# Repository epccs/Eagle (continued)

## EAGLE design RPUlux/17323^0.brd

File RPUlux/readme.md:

# RPUlux

This circuit board has six 330mA LED channels each done with AL8805W5-7, it uses the ATmega328p's six PWM pins to control the switch mode current sources that can be enabled and disabled at 500Hz. A few pins also go to other connectors and allow some digital input-output or analog input options. The IO is also level shifted to work with the two onboard current sources.

[Software]

[Software]: https://github.com/epccs/RPUlux/

[Bom]

[Bom]: https://github.com/epccs/RPUlux/

[OSHPark]s

[OSHPark]: https://oshpark.com/shared_projects/fMLOXrKi

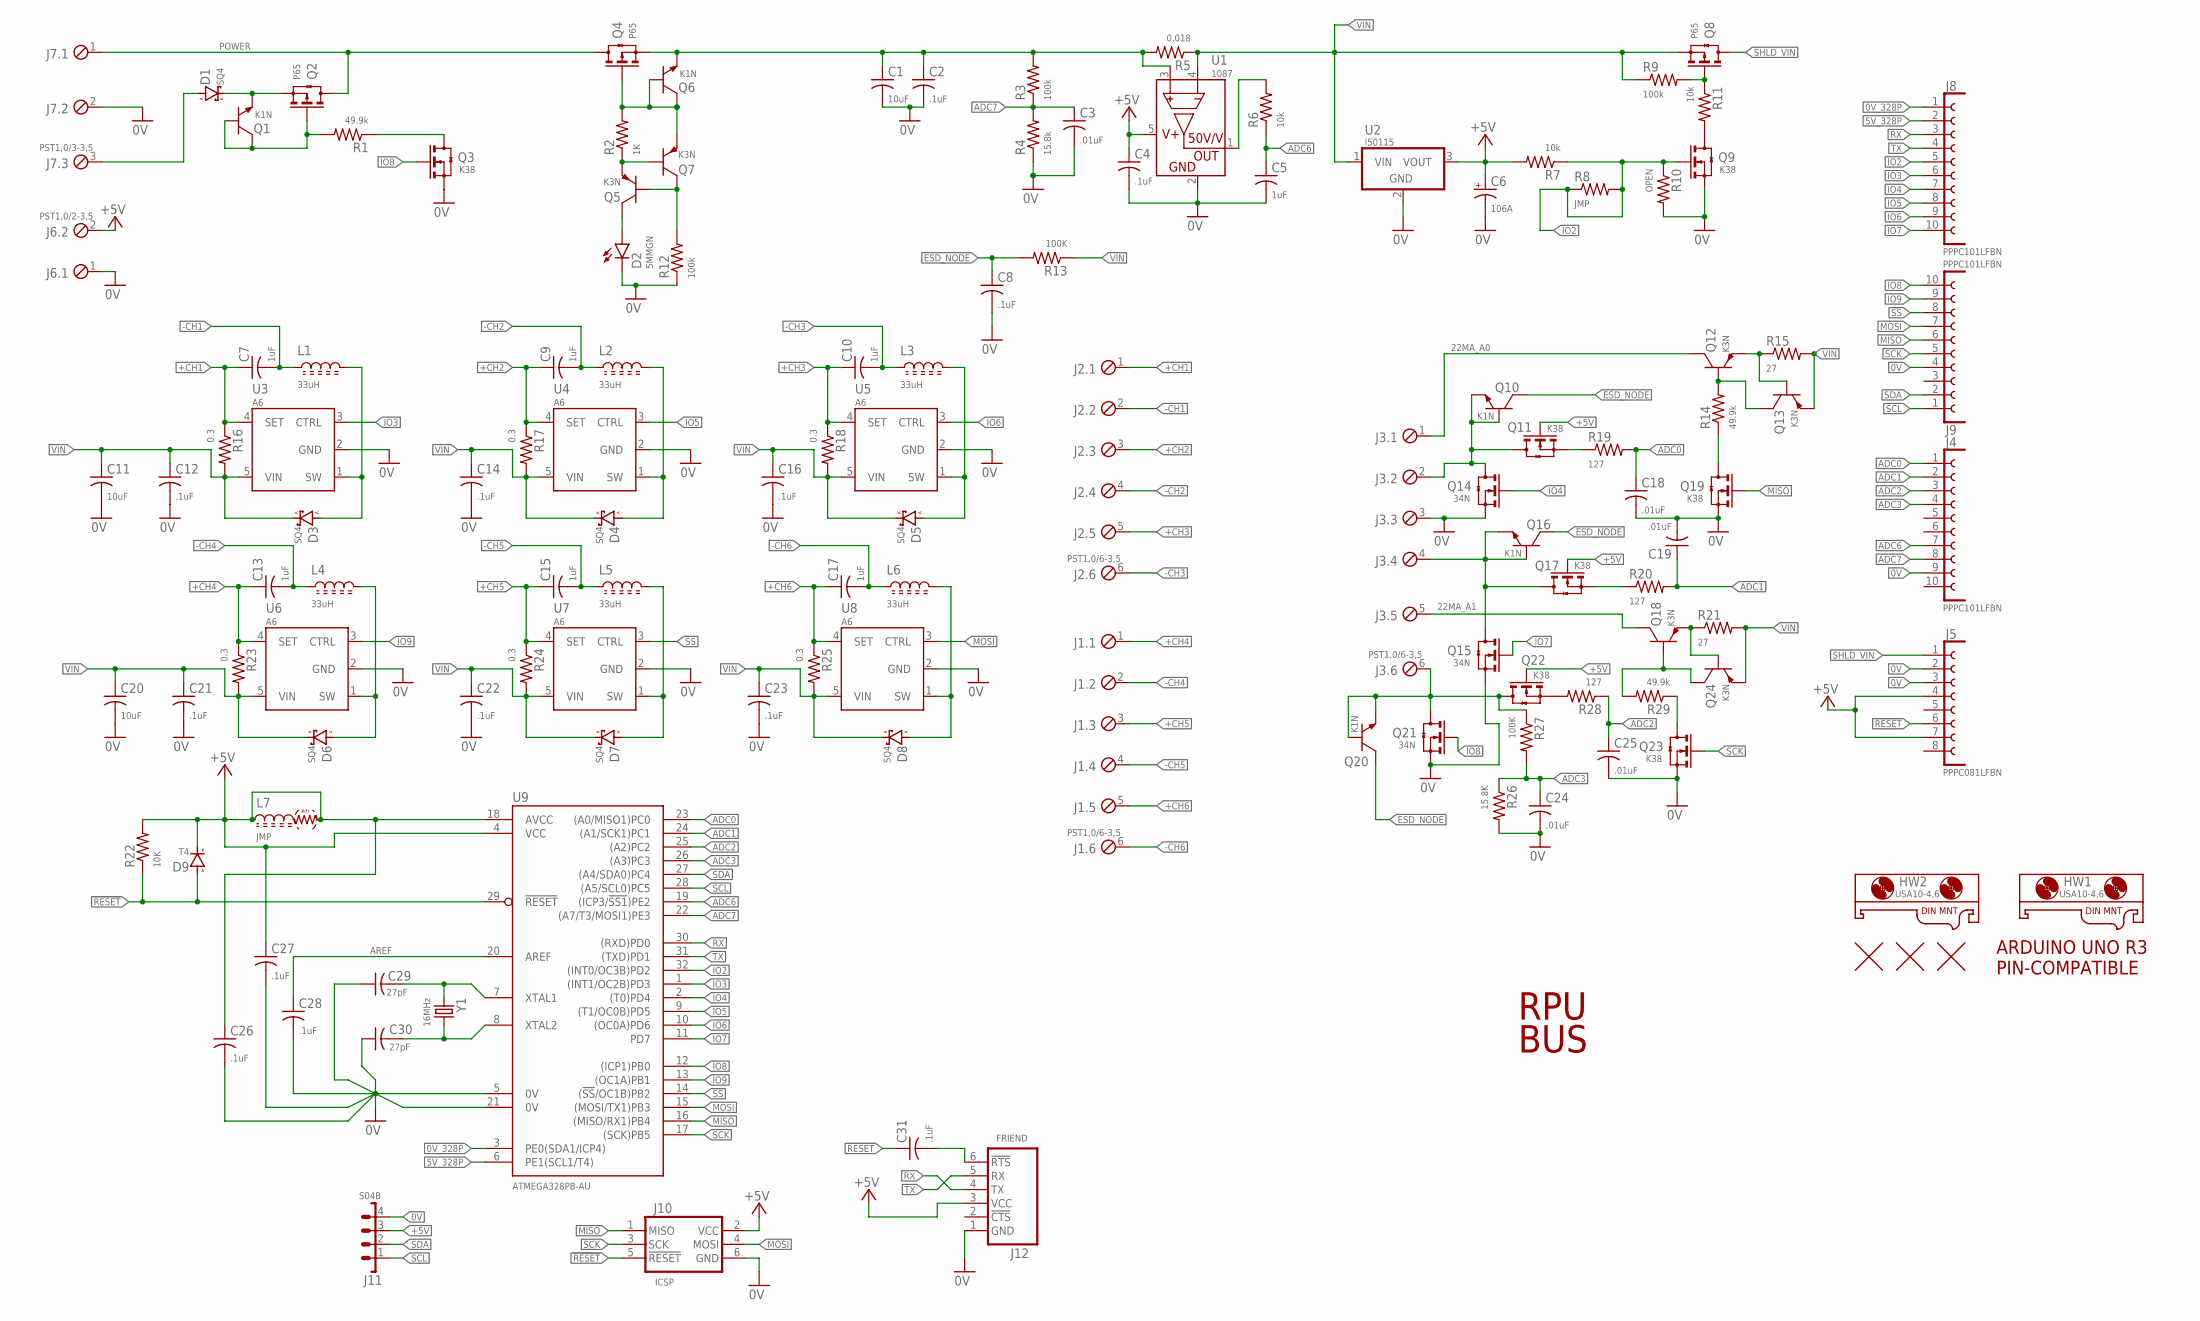
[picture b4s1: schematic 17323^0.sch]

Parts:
C1, C11, C20: 10uF; C1206(3216)
C2: .1uF; C0805(2012)
C3, C18, C19, C24, C25: .01uF; C0603(1608)
C4, C8, C12, C14, C16, C21, C22, C23, C26, C27, C28, C31: .1uF; C0603(1608)
C5, C7, C9, C10, C13, C15, C17: 1uF; C0805(2012)
C6: 106A; 3216
C29, C30: 27pF; C0603(1608)
D1, D3, D4, D5, D6, D7, D8: SQ4; SMA
D2: 5MMGN; LED5MM
D9: T4; SOD123
HW1, HW2: USA10-4,6; USA10
J1, J2, J3: PST1,0/6-3,5; MCV6
J4, J8, J9: PPPC101LFBN; F1X10
J5: PPPC081LFBN; F1X8
J6: PST1,0/2-3,5; MCV2
J7: PST1,0/3-3,5; MCV3
J10: ICSP; ISP
J11: S04B; B04B
J12: FRIEND
L1, L2, L3, L4, L5, L6: 33uH; L2424
L7: JMP; C0805(2012)
Q1, Q6, Q10, Q16, Q20: K1N; SOT23
Q2, Q4, Q8: P65; SOT23
Q3, Q9, Q11, Q17, Q19, Q22, Q23: K38; SOT23
Q5, Q7, Q12, Q13, Q18, Q24: K3N; SOT23
Q14, Q15, Q21: 34N; SOT23
R1, R14, R29: 49.9k; C0805(2012)
R2: 1K; C0805(2012)
R3, R9, R12: 100k; C0805(2012)
R4: 15.8k; C0805(2012)
R5: 0.018; C1210(3225)
R6, R7, R11: 10k; C0805(2012)
R8: JMP; C0805(2012)
R10: OPEN; C0805(2012)
R13, R27: 100K; C0805(2012)
R15, R21: 27; C0805(2012)
R16, R17, R18, R23, R24, R25: 0.3; C1210(3225)
R19, R20, R28: 127; C0805(2012)
R22: 10K; C0805(2012)
R26: 15.8K; C0805(2012)
U1: 1087; SOT23-5
U2: I50115; OKI-78SR-H
U3, U4, U5, U6, U7, U8: A6; SOT23-5
U9: ATMEGA328PB-AU; TQFP32-08
U$1: ARDUINO-UNO; ARDUINO_UNO
U$2, U$3, U$4: FIDUCIAL1.27; FIDUCIAL-1.27
Y1: 16MHz; CSM-3X

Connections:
0V: C1.2, C2.2, C3.2, C4.2, C5.2, C6.-, C8.2, C11.2, C12.2, C14.2, C16.2, C18.2, C19.2, C20.2, C21.2, C22.2, C23.2, C24.2, C25.2, C26.2, C27.2, C28.2, C29.1, C30.1, D2.K, J3.3, J4.9, J5.2, J5.3, J6.1, J7.2, J9.4, J10.6 (GND), J11.4, J12.1 (GND), Q3.2(S) (S), Q9.2(S) (S), Q14.2(S) (S), Q15.2(S) (S), Q19.2(S) (S), Q21.2(S) (S), Q23.2(S) (S), R4.1, R10.2, R12.1, R26.2, U1.2 (GND), U2.2 (GND), U3.2 (GND), U4.2 (GND), U5.2 (GND), U6.2 (GND), U7.2 (GND), U8.2 (GND), U9.5 (0V), U9.21 (0V)
0V_328P: J8.1, U9.3 (PE0(SDA1/ICP4))
5V_328P: J8.2, U9.6 (PE1(SCL1/T4))
22MA_A0: J3.1, Q12.C
22MA_A1: J3.5, Q18.C
!RESET!: C31.1, D9.A, J5.6, J10.5 (!RESET), R22.1, U9.29 (!RESET)
!SS: J9.8, U7.3 (CTRL), U9.14 ((!SS!/OC1B)PB2)
+5V: C4.1, C6.+, C26.1, C27.1, D9.C (K), J5.4, J5.7, J6.2, J10.2 (VCC), J11.3, J12.3 (VCC), L7.1, L7.2, Q11.1(G) (G), Q17.1(G) (G), Q22.1(G) (G), R7.2, R22.2, U1.5 (VCC), U2.3 (VOUT), U9.4 (VCC), U9.18 (AVCC)
+CH1: C7.1, J2.1, R16.1, U3.4 (SET)
+CH2: C9.1, J2.3, R17.1, U4.4 (SET)
+CH3: C10.1, J2.5, R18.1, U5.4 (SET)
+CH4: C13.1, J1.1, R23.1, U6.4 (SET)
+CH5: C15.1, J1.3, R24.1, U7.4 (SET)
+CH6: C17.1, J1.5, R25.1, U8.4 (SET)
-CH1: C7.2, J2.2, L1.1
-CH2: C9.2, J2.4, L2.1
-CH3: C10.2, J2.6, L3.1
-CH4: C13.2, J1.2, L4.1
-CH5: C15.2, J1.4, L5.1
-CH6: C17.2, J1.6, L6.1
ADC0: C18.1, J4.1, R19.2, U9.23 ((A0/MISO1)PC0)
ADC1: C19.1, J4.2, R20.2, U9.24 ((A1/SCK1)PC1)
ADC2: C25.1, J4.3, R28.1, U9.25 ((A2)PC2)
ADC3: C24.1, J4.4, R26.1, R27.2, U9.26 ((A3)PC3)
ADC6: C5.1, J4.7, R6.1, U9.19 ((ICP3/!SS1!)PE2)
ADC7: C3.1, J4.8, R3.1, R4.2, U9.22 ((A7/T3/MOSI1)PE3)
AREF: C28.1, U9.20 (AREF)
ESD_NODE: C8.1, Q10.C, Q16.C, Q20.C, R13.2
IO2: J8.5, Q9.1(G) (G), R7.1, R8.1, R8.2, R10.1, U9.32 ((INT0/OC3B)PD2)
IO3: J8.6, U3.3 (CTRL), U9.1 ((INT1/OC2B)PD3)
IO4: J8.7, Q14.1(G) (G), U9.2 ((T0)PD4)
IO5: J8.8, U4.3 (CTRL), U9.9 ((T1/OC0B)PD5)
IO6: J8.9, U5.3 (CTRL), U9.10 ((OC0A)PD6)
IO7: J8.10, Q15.1(G) (G), U9.11 (PD7)
IO8: J9.10, Q3.1(G) (G), Q21.1(G) (G), U9.12 ((ICP1)PB0)
IO9: J9.9, U6.3 (CTRL), U9.13 ((OC1A)PB1)
MISO: J9.6, J10.1 (MISO), Q19.1(G) (G), U9.16 ((MISO/RX1)PB4)
MOSI: J9.7, J10.4 (MOSI), U8.3 (CTRL), U9.15 ((MOSI/TX1)PB3)
unnamed: Q22.2(S) (S), R28.2
unnamed: Q8.1(G) (G), R9.2, R11.1
unnamed: D3.A, L1.2, U3.1 (SW)
unnamed: Q9.3(D) (D), R11.2
unnamed: Q5.B, Q7.C, R12.2
unnamed: Q4.1(G) (G), Q6.B, Q6.C, Q7.E, R2.2
unnamed: D2.A, Q5.C
unnamed: R6.2, U1.1 (OUT)
unnamed: J3.6, Q20.B, Q20.E, Q21.3(D) (D), Q22.3(D) (D), R27.1
unnamed: Q5.E, Q7.B, R2.1
unnamed: D6.A, L4.2, U6.1 (SW)
unnamed: J3.4, Q15.3(D) (D), Q16.B, Q16.E, Q17.3(D) (D)
unnamed: Q17.2(S) (S), R20.1
unnamed: Q11.2(S) (S), R19.1
unnamed: J3.2, Q10.B, Q10.E, Q11.3(D) (D), Q14.3(D) (D)
unnamed: D4.A, L2.2, U4.1 (SW)
unnamed: D7.A, L5.2, U7.1 (SW)
unnamed: D5.A, L3.2, U5.1 (SW)
unnamed: Q23.3(D) (D), R29.1
unnamed: Q12.E, Q13.B, R15.1
unnamed: Q19.3(D) (D), R14.1
unnamed: D8.A, L6.2, U8.1 (SW)
unnamed: Q12.B, Q13.C, R14.2
unnamed: D1.A, J7.3
unnamed: C31.2, J12.6 (!RTS)
unnamed: Q18.E, Q24.B, R21.1
unnamed: Q18.B, Q24.C, R29.2
unnamed: D1.K, Q1.E, Q2.2(S) (S)
unnamed: Q1.B, Q1.C, Q2.1(G) (G), R1.2
unnamed: Q3.3(D) (D), R1.1
unnamed: C29.2, U9.7 (XTAL1), Y1.1
unnamed: C30.2, U9.8 (XTAL2), Y1.2
POWER: J7.1, Q2.3(D) (D), Q4.3(D) (D)
RX: J8.3, J12.4 (TX), U9.30 ((RXD)PD0)
SCK: J9.5, J10.3 (SCK), Q23.1(G) (G), U9.17 ((SCK)PB5)
SCL: J9.1, J11.1, U9.28 ((A5/SCL0)PC5)
SDA: J9.2, J11.2, U9.27 ((A4/SDA0)PC4)
SHLD_VIN: J5.1, Q8.3(D) (D)
TX: J8.4, J12.5 (RX), U9.31 ((TXD)PD1)
VIN: C11.1, C12.1, C14.1, C16.1, C20.1, C21.1, C22.1, C23.1, D3.K, D4.K, D5.K, D6.K, D7.K, D8.K, Q8.2(S) (S), Q13.E, Q24.E, R5.1, R9.1, R13.1, R15.2, R16.2, R17.2, R18.2, R21.2, R23.2, R24.2, R25.2, U1.4 (S-), U2.1 (VIN), U3.5 (VIN), U4.5 (VIN), U5.5 (VIN), U6.5 (VIN), U7.5 (VIN), U8.5 (VIN)
VIN_S: C1.1, C2.1, Q4.2(S) (S), Q6.E, R3.2, R5.2, U1.3 (S+)

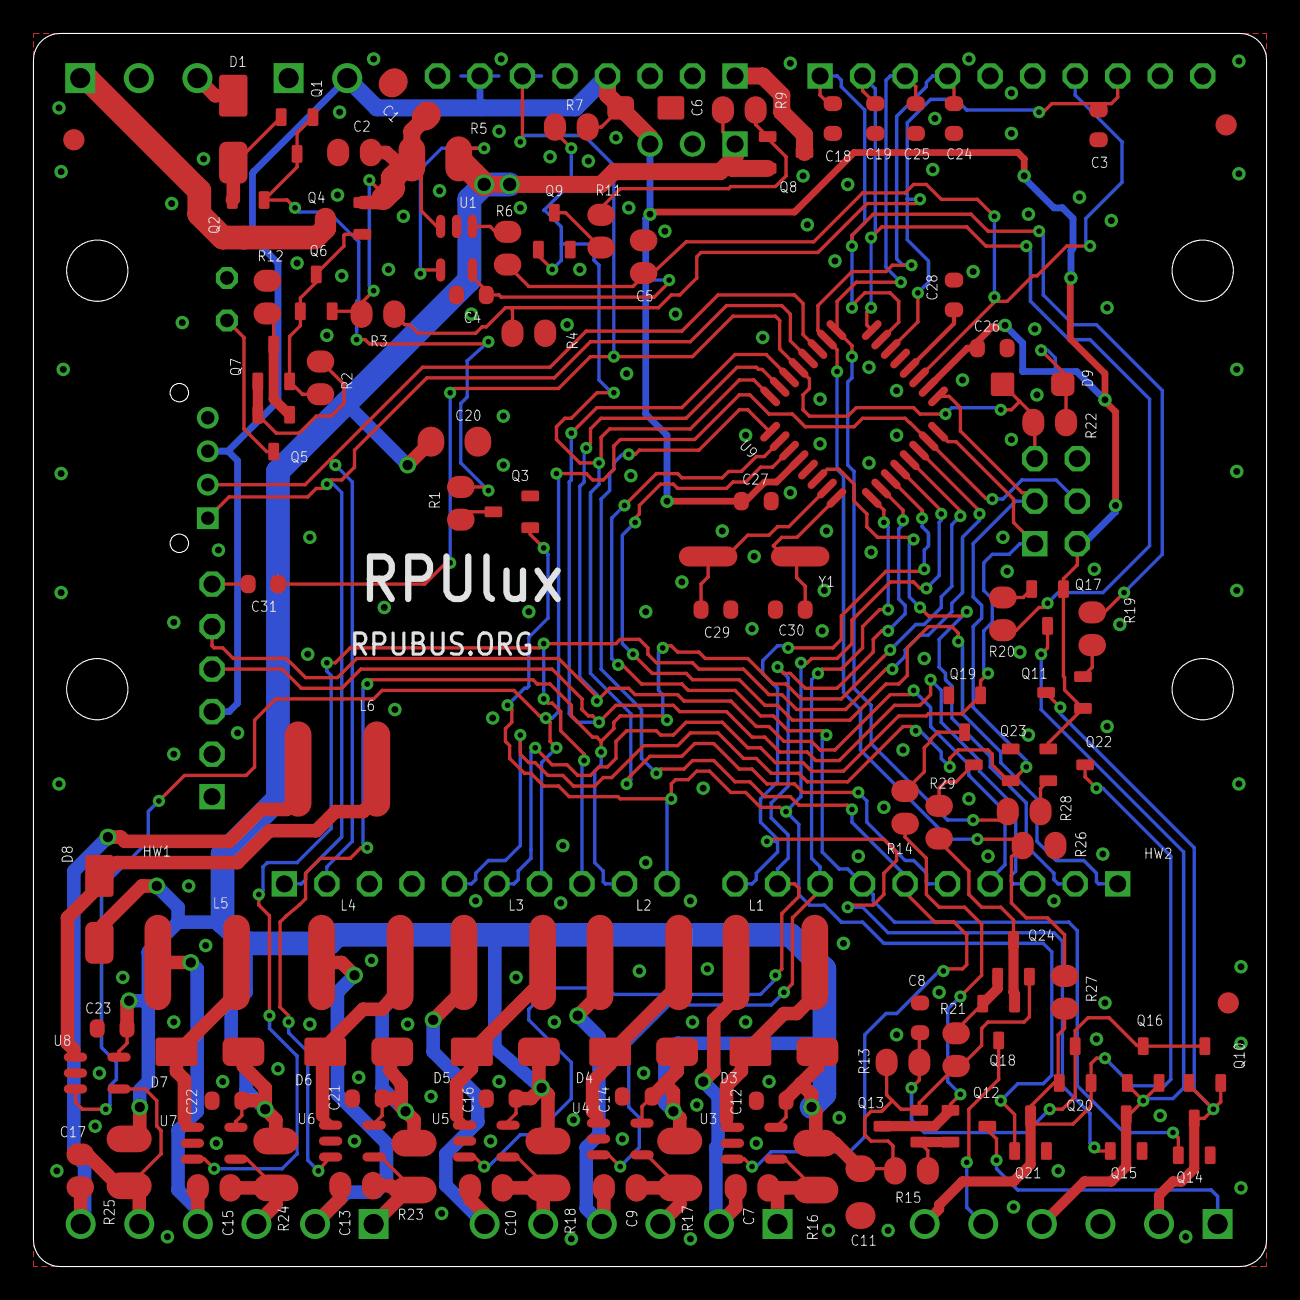
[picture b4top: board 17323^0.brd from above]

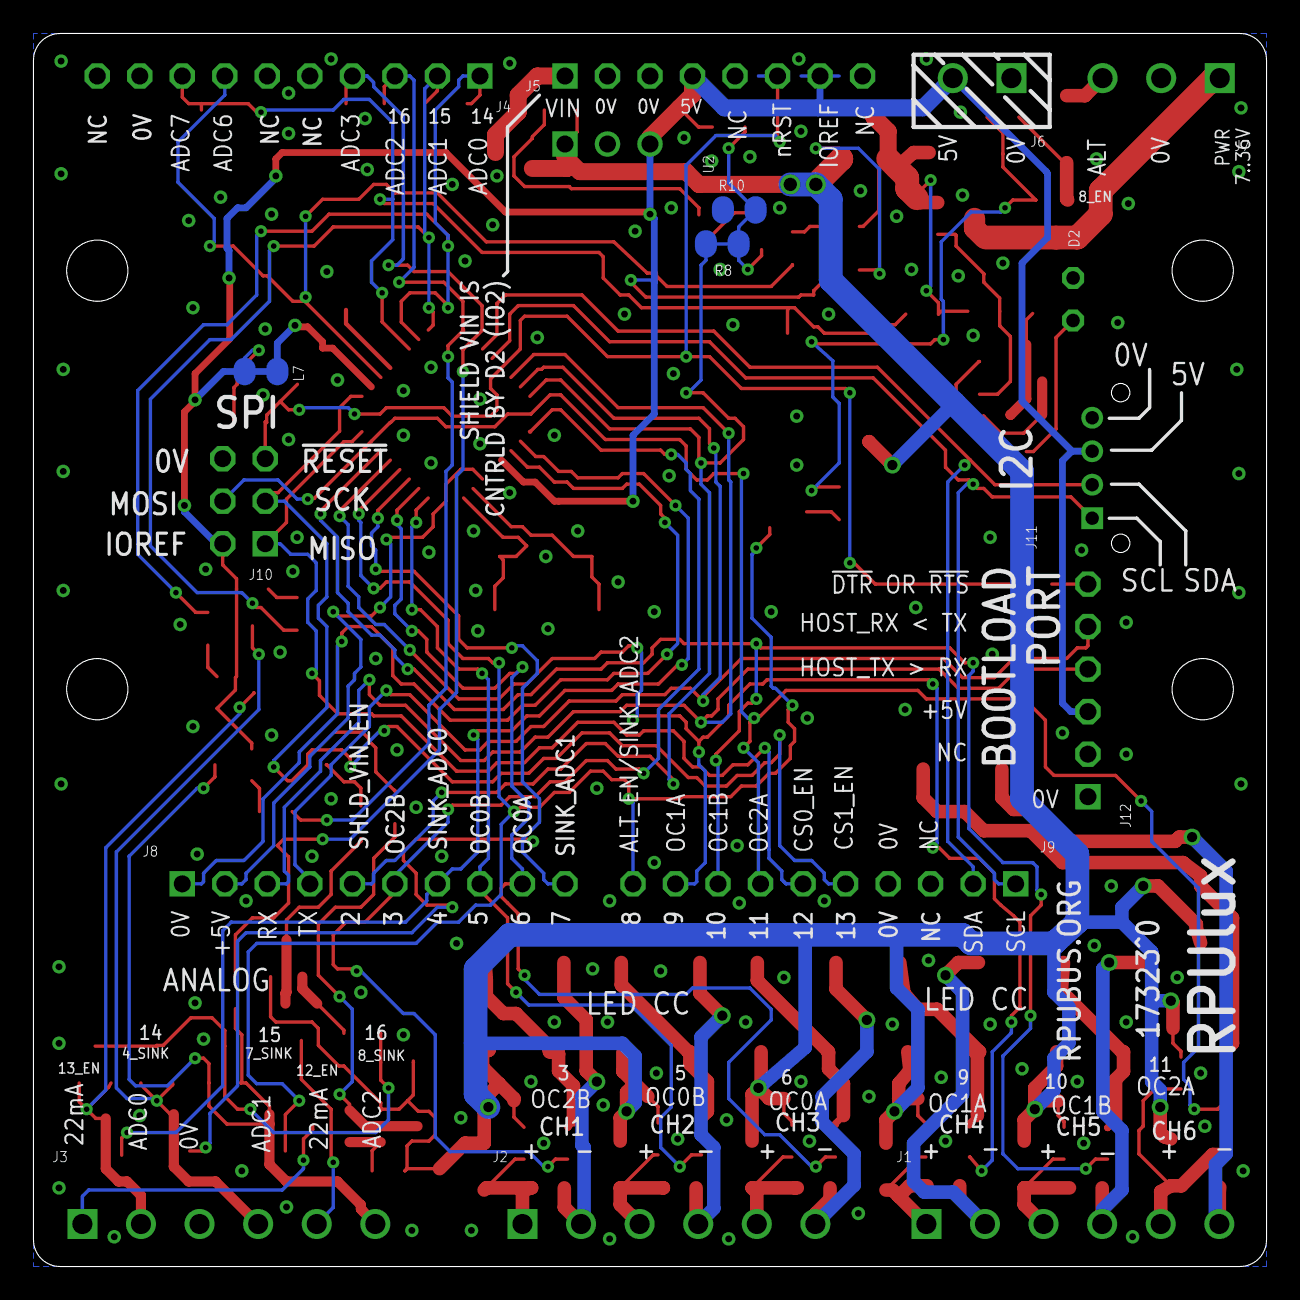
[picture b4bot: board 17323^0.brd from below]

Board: 2 copper layers, 73.7 x 73.7 mm, 128 parts (18 on the bottom side), 79 nets.

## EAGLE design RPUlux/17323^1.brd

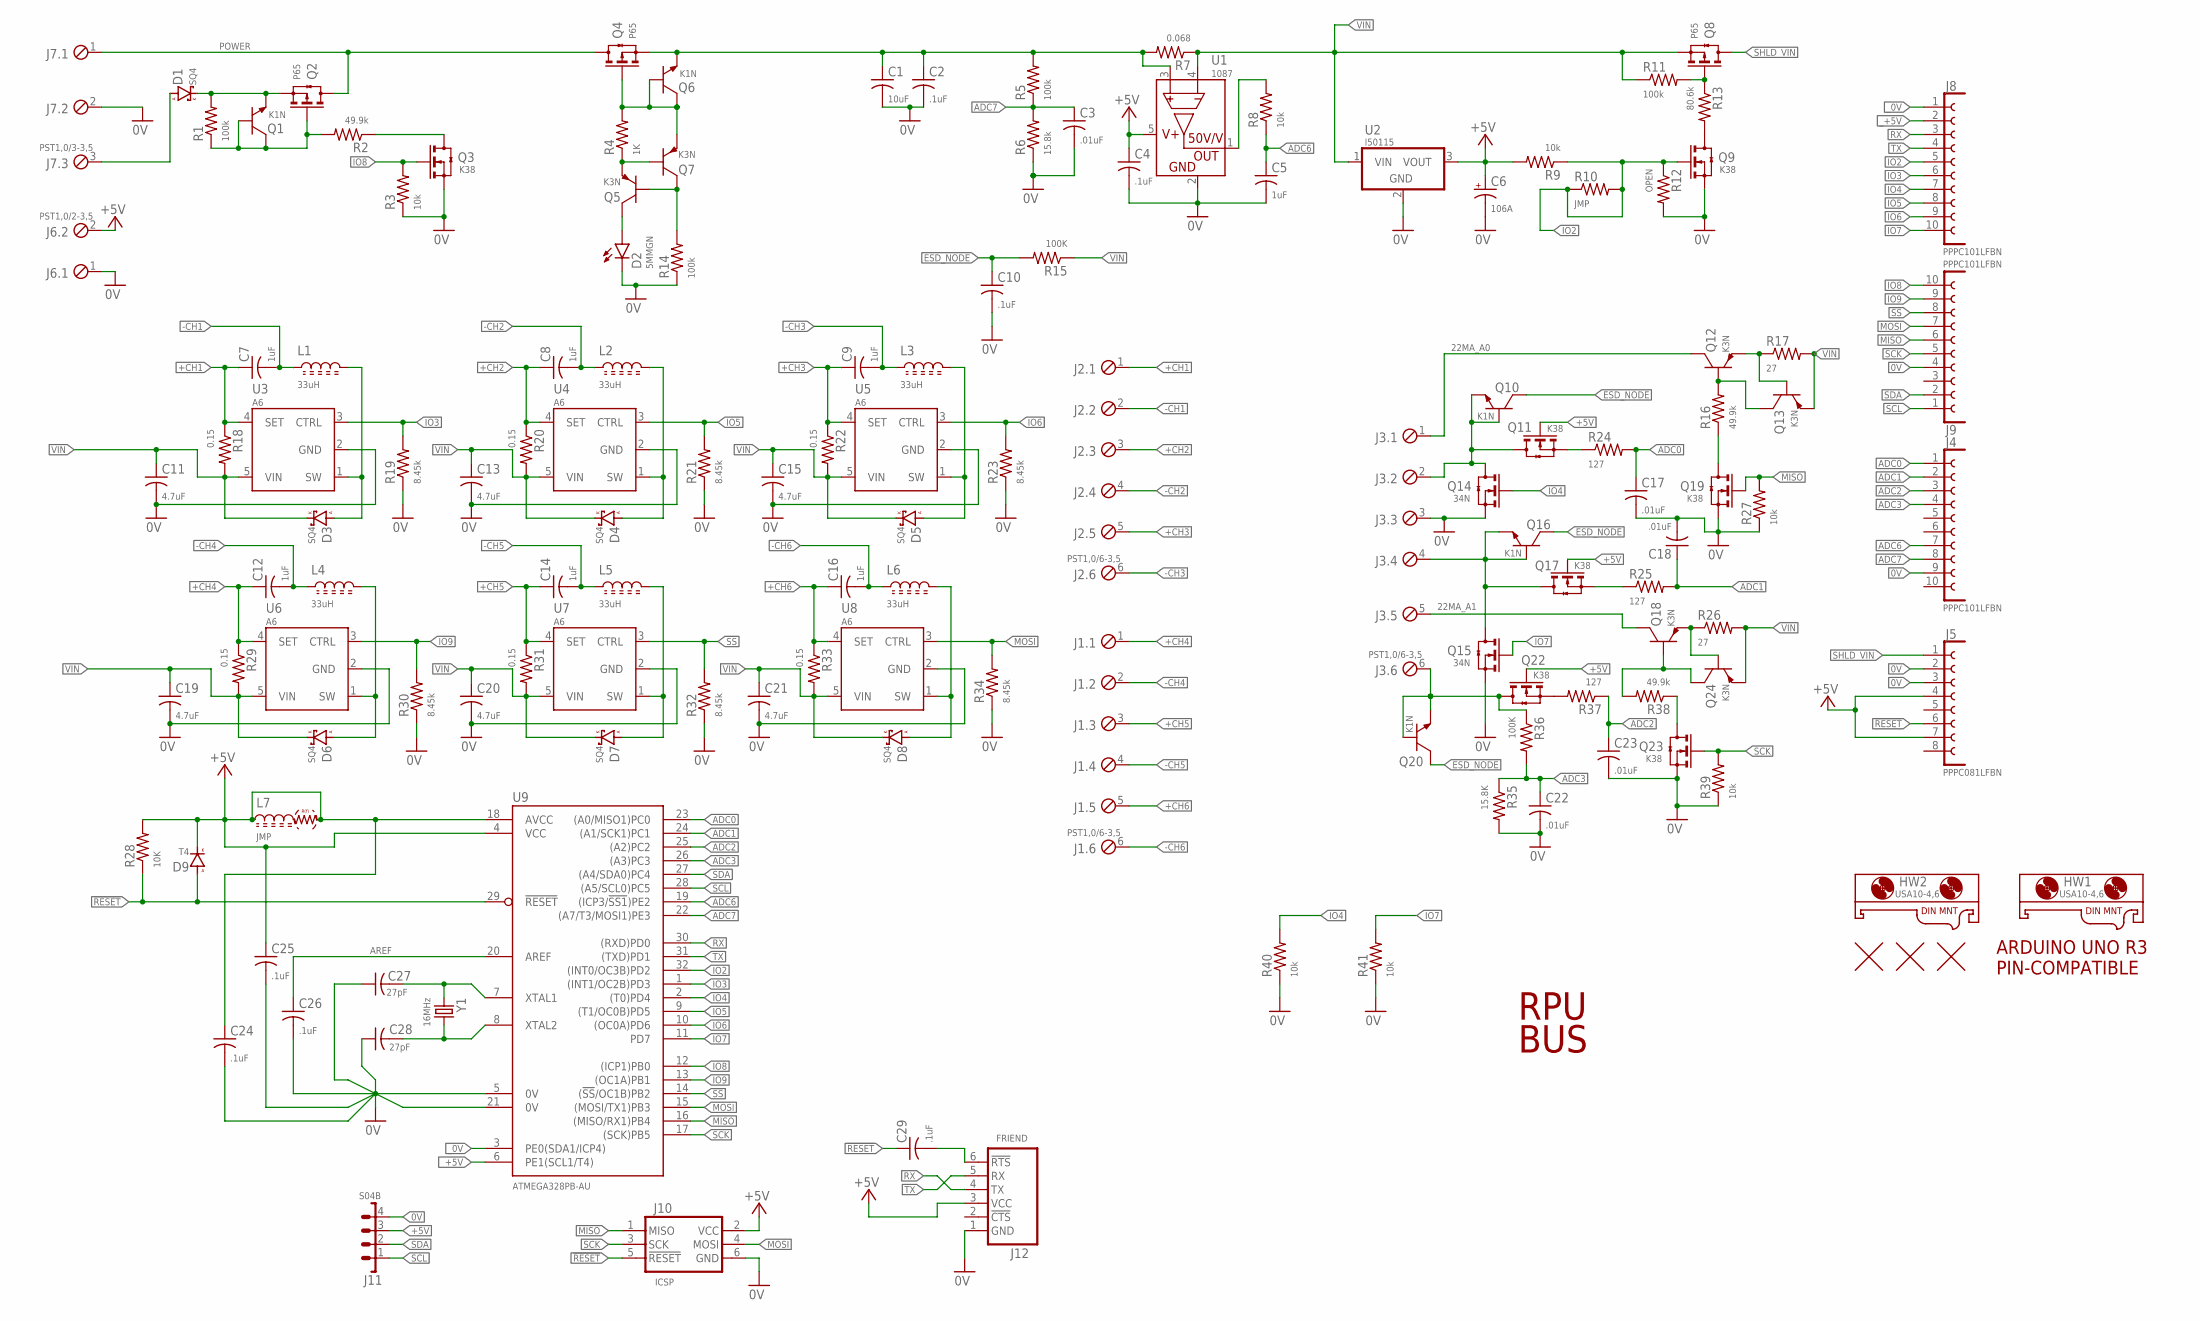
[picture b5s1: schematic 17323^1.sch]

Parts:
C1: 10uF; C1206(3216)
C2: .1uF; C0805(2012)
C3, C17, C18, C22, C23: .01uF; C0603(1608)
C4, C10, C24, C25, C26, C29: .1uF; C0603(1608)
C5, C7, C8, C9, C12, C14, C16: 1uF; C0805(2012)
C6: 106A; 3216
C11, C13, C15, C19, C20, C21: 4.7uF; C1206(3216)
C27, C28: 27pF; C0603(1608)
D1, D3, D4, D5, D6, D7, D8: SQ4; SMA
D2: 5MMGN; LED5MM
D9: T4; SOD123
HW1, HW2: USA10-4,6; USA10
J1, J2, J3: PST1,0/6-3,5; MCV6
J4, J8, J9: PPPC101LFBN; F1X10
J5: PPPC081LFBN; F1X8
J6: PST1,0/2-3,5; MCV2
J7: PST1,0/3-3,5; MCV3
J10: ICSP; ISP
J11: S04B; B04B
J12: FRIEND
L1, L2, L3, L4, L5, L6: 33uH; L2424
L7: JMP; C0805(2012)
Q1, Q6, Q10, Q16, Q20: K1N; SOT23
Q2, Q4, Q8: P65; SOT23
Q3, Q9, Q11, Q17, Q19, Q22, Q23: K38; SOT23
Q5, Q7, Q12, Q13, Q18, Q24: K3N; SOT23
Q14, Q15: 34N; SOT23
R1, R5, R11, R14: 100k; C0805(2012)
R2, R16, R38: 49.9k; C0805(2012)
R3, R8, R9, R27, R39, R40, R41: 10k; C0805(2012)
R4: 1K; C0805(2012)
R6: 15.8k; C0805(2012)
R7: 0.068; C1210(3225)
R10: JMP; C0805(2012)
R12: OPEN; C0805(2012)
R13: 80.6k; C0805(2012)
R15, R36: 100K; C0805(2012)
R17, R26: 27; C0805(2012)
R18, R20, R22, R29, R31, R33: 0.15; C1210(3225)
R19, R21, R23, R30, R32, R34: 8.45k; C0805(2012)
R24, R25, R37: 127; C0805(2012)
R28: 10K; C0805(2012)
R35: 15.8K; C0805(2012)
U1: 1087; SOT23-5
U2: I50115; OKI-78SR-H
U3, U4, U5, U6, U7, U8: A6; SOT23-5
U9: ATMEGA328PB-AU; TQFP32-08
U$1: ARDUINO-UNO; ARDUINO_UNO
U$2, U$3, U$4: FIDUCIAL1.27; FIDUCIAL-1.27
Y1: 16MHz; CSM-3X

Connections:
0V: C1.2, C2.2, C3.2, C4.2, C5.2, C6.-, C10.2, C11.2, C13.2, C15.2, C17.2, C18.2, C19.2, C20.2, C21.2, C22.2, C23.2, C24.2, C25.2, C26.2, C27.1, C28.1, D2.K, J3.3, J4.9, J5.2, J5.3, J6.1, J7.2, J9.4, J10.6 (GND), J11.4, J12.1 (GND), Q3.2(S) (S), Q9.2(S) (S), Q14.2(S) (S), Q15.2(S) (S), Q19.2(S) (S), Q23.2(S) (S), R3.1, R6.1, R12.2, R14.1, R19.1, R21.1, R23.1, R27.1, R30.1, R32.1, R34.1, R35.2, R39.1, R40.1, R41.1, U1.2 (GND), U2.2 (GND), U3.2 (GND), U4.2 (GND), U5.2 (GND), U6.2 (GND), U7.2 (GND), U8.2 (GND), U9.5 (0V), U9.21 (0V)
22MA_A0: J3.1, Q12.C
22MA_A1: J3.5, Q18.C
!RESET!: C29.1, D9.A, J5.6, J10.5 (!RESET), R28.1, U9.29 (!RESET)
!SS: J9.8, R32.2, U7.3 (CTRL), U9.14 ((!SS!/OC1B)PB2)
+5V: C4.1, C6.+, C24.1, C25.1, D9.C (K), J5.4, J5.7, J6.2, J10.2 (VCC), J11.3, J12.3 (VCC), L7.1, L7.2, Q11.1(G) (G), Q17.1(G) (G), Q22.1(G) (G), R9.2, R28.2, U1.5 (VCC), U2.3 (VOUT), U9.4 (VCC), U9.18 (AVCC)
+CH1: C7.1, J2.1, R18.1, U3.4 (SET)
+CH2: C8.1, J2.3, R20.1, U4.4 (SET)
+CH3: C9.1, J2.5, R22.1, U5.4 (SET)
+CH4: C12.1, J1.1, R29.1, U6.4 (SET)
+CH5: C14.1, J1.3, R31.1, U7.4 (SET)
+CH6: C16.1, J1.5, R33.1, U8.4 (SET)
-CH1: C7.2, J2.2, L1.1
-CH2: C8.2, J2.4, L2.1
-CH3: C9.2, J2.6, L3.1
-CH4: C12.2, J1.2, L4.1
-CH5: C14.2, J1.4, L5.1
-CH6: C16.2, J1.6, L6.1
ADC0: C17.1, J4.1, R24.2, U9.23 ((A0/MISO1)PC0)
ADC1: C18.1, J4.2, R25.2, U9.24 ((A1/SCK1)PC1)
ADC2: C23.1, J4.3, R37.1, U9.25 ((A2)PC2)
ADC3: C22.1, J4.4, R35.1, R36.2, U9.26 ((A3)PC3)
ADC6: C5.1, J4.7, R8.1, U9.19 ((ICP3/!SS1!)PE2)
ADC7: C3.1, J4.8, R5.1, R6.2, U9.22 ((A7/T3/MOSI1)PE3)
AREF: C26.1, U9.20 (AREF)
ESD_NODE: C10.1, Q10.C, Q16.C, Q20.C, R15.2
IO2: J8.5, Q9.1(G) (G), R9.1, R10.1, R10.2, R12.1, U9.32 ((INT0/OC3B)PD2)
IO3: J8.6, R19.2, U3.3 (CTRL), U9.1 ((INT1/OC2B)PD3)
IO4: J8.7, Q14.1(G) (G), R40.2, U9.2 ((T0)PD4)
IO5: J8.8, R21.2, U4.3 (CTRL), U9.9 ((T1/OC0B)PD5)
IO6: J8.9, R23.2, U5.3 (CTRL), U9.10 ((OC0A)PD6)
IO7: J8.10, Q15.1(G) (G), R41.2, U9.11 (PD7)
IO8: J9.10, Q3.1(G) (G), R3.2, U9.12 ((ICP1)PB0)
IO9: J9.9, R30.2, U6.3 (CTRL), U9.13 ((OC1A)PB1)
MISO: J9.6, J10.1 (MISO), Q19.1(G) (G), R27.2, U9.16 ((MISO/RX1)PB4)
MOSI: J9.7, J10.4 (MOSI), R34.2, U8.3 (CTRL), U9.15 ((MOSI/TX1)PB3)
unnamed: Q22.2(S) (S), R37.2
unnamed: Q8.1(G) (G), R11.2, R13.1
unnamed: D3.A, L1.2, U3.1 (SW)
unnamed: Q9.3(D) (D), R13.2
unnamed: Q5.B, Q7.C, R14.2
unnamed: Q4.1(G) (G), Q6.B, Q6.C, Q7.E, R4.2
unnamed: D2.A, Q5.C
unnamed: R8.2, U1.1 (OUT)
unnamed: J3.6, Q20.B, Q20.E, Q22.3(D) (D), R36.1
unnamed: Q5.E, Q7.B, R4.1
unnamed: D6.A, L4.2, U6.1 (SW)
unnamed: J3.4, Q15.3(D) (D), Q16.B, Q16.E, Q17.3(D) (D)
unnamed: Q17.2(S) (S), R25.1
unnamed: Q11.2(S) (S), R24.1
unnamed: J3.2, Q10.B, Q10.E, Q11.3(D) (D), Q14.3(D) (D)
unnamed: D4.A, L2.2, U4.1 (SW)
unnamed: D7.A, L5.2, U7.1 (SW)
unnamed: D5.A, L3.2, U5.1 (SW)
unnamed: Q23.3(D) (D), R38.1
unnamed: Q12.E, Q13.B, R17.1
unnamed: Q19.3(D) (D), R16.1
unnamed: D8.A, L6.2, U8.1 (SW)
unnamed: Q12.B, Q13.C, R16.2
unnamed: D1.A, J7.3
unnamed: C29.2, J12.6 (!RTS)
unnamed: Q18.E, Q24.B, R26.1
unnamed: Q18.B, Q24.C, R38.2
unnamed: D1.K, Q1.E, Q2.2(S) (S), R1.2
unnamed: Q1.B, Q1.C, Q2.1(G) (G), R1.1, R2.2
unnamed: Q3.3(D) (D), R2.1
unnamed: C27.2, U9.7 (XTAL1), Y1.1
unnamed: C28.2, U9.8 (XTAL2), Y1.2
POWER: J7.1, Q2.3(D) (D), Q4.3(D) (D)
RX: J8.3, J12.4 (TX), U9.30 ((RXD)PD0)
SCK: J9.5, J10.3 (SCK), Q23.1(G) (G), R39.2, U9.17 ((SCK)PB5)
SCL: J9.1, J11.1, U9.28 ((A5/SCL0)PC5)
SDA: J9.2, J11.2, U9.27 ((A4/SDA0)PC4)
SHLD_VIN: J5.1, Q8.3(D) (D)
TX: J8.4, J12.5 (RX), U9.31 ((TXD)PD1)
VIN: C11.1, C13.1, C15.1, C19.1, C20.1, C21.1, D3.K, D4.K, D5.K, D6.K, D7.K, D8.K, Q8.2(S) (S), Q13.E, Q24.E, R7.1, R11.1, R15.1, R17.2, R18.2, R20.2, R22.2, R26.2, R29.2, R31.2, R33.2, U1.4 (S-), U2.1 (VIN), U3.5 (VIN), U4.5 (VIN), U5.5 (VIN), U6.5 (VIN), U7.5 (VIN), U8.5 (VIN)
VIN_S: C1.1, C2.1, Q4.2(S) (S), Q6.E, R5.2, R7.2, U1.3 (S+)
_0V: J8.1, U9.3 (PE0(SDA1/ICP4))
_+5V: J8.2, U9.6 (PE1(SCL1/T4))

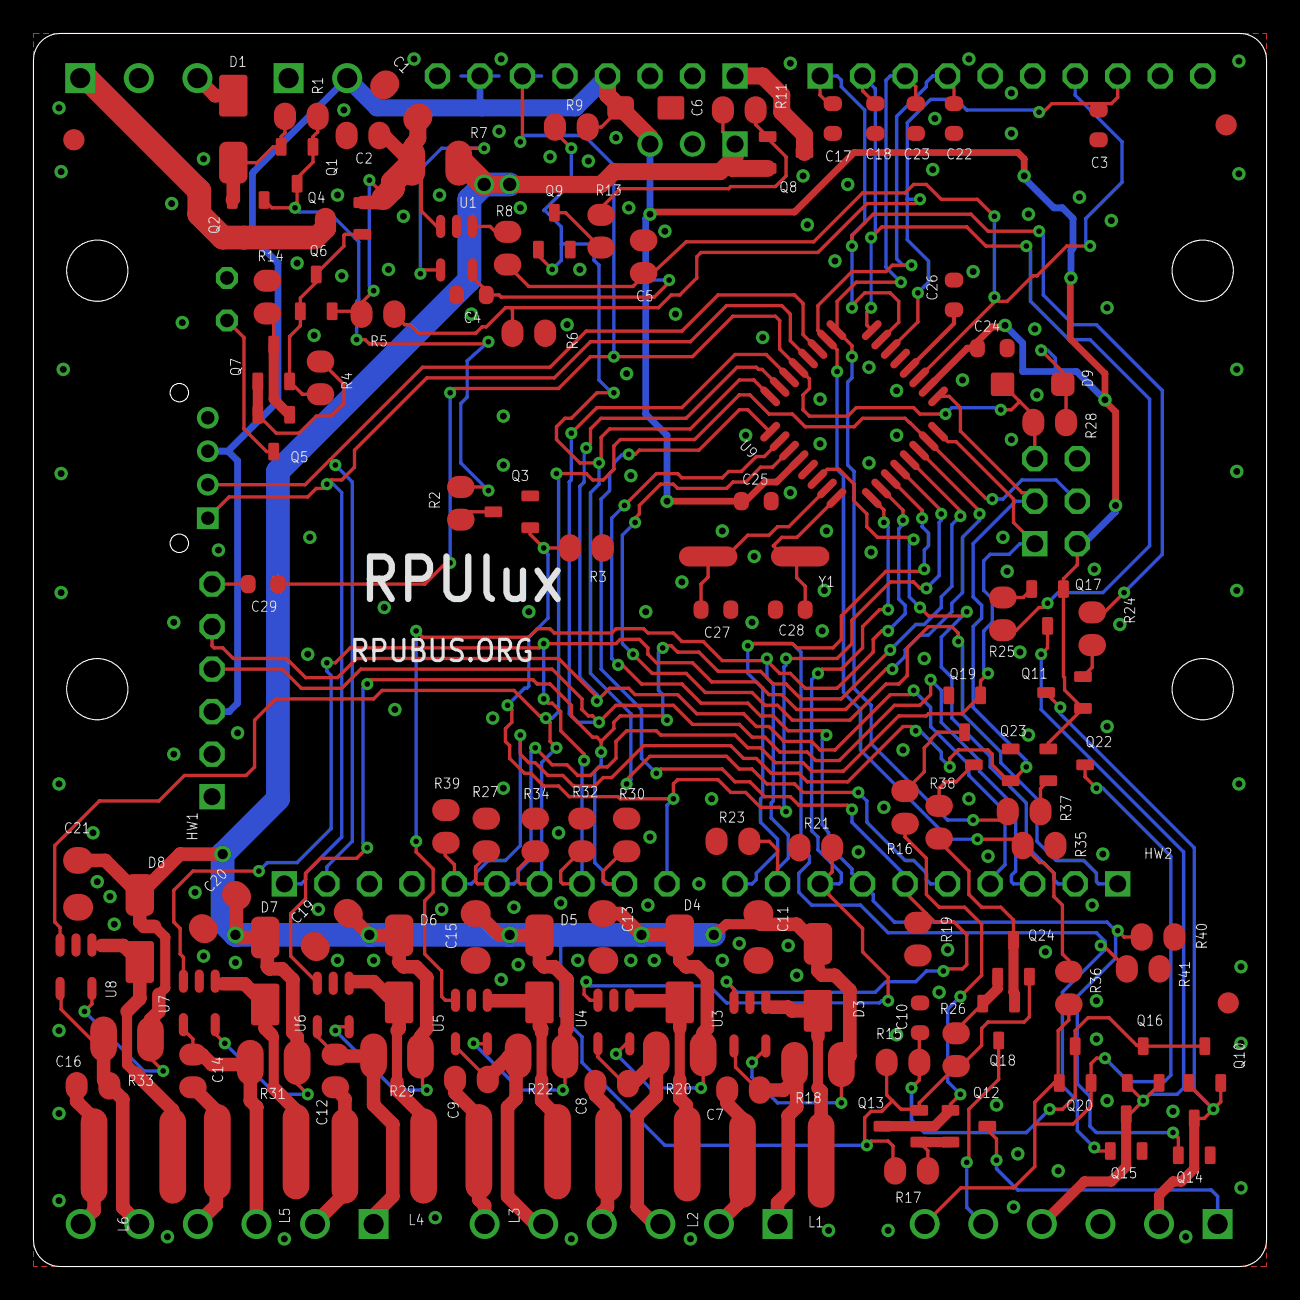
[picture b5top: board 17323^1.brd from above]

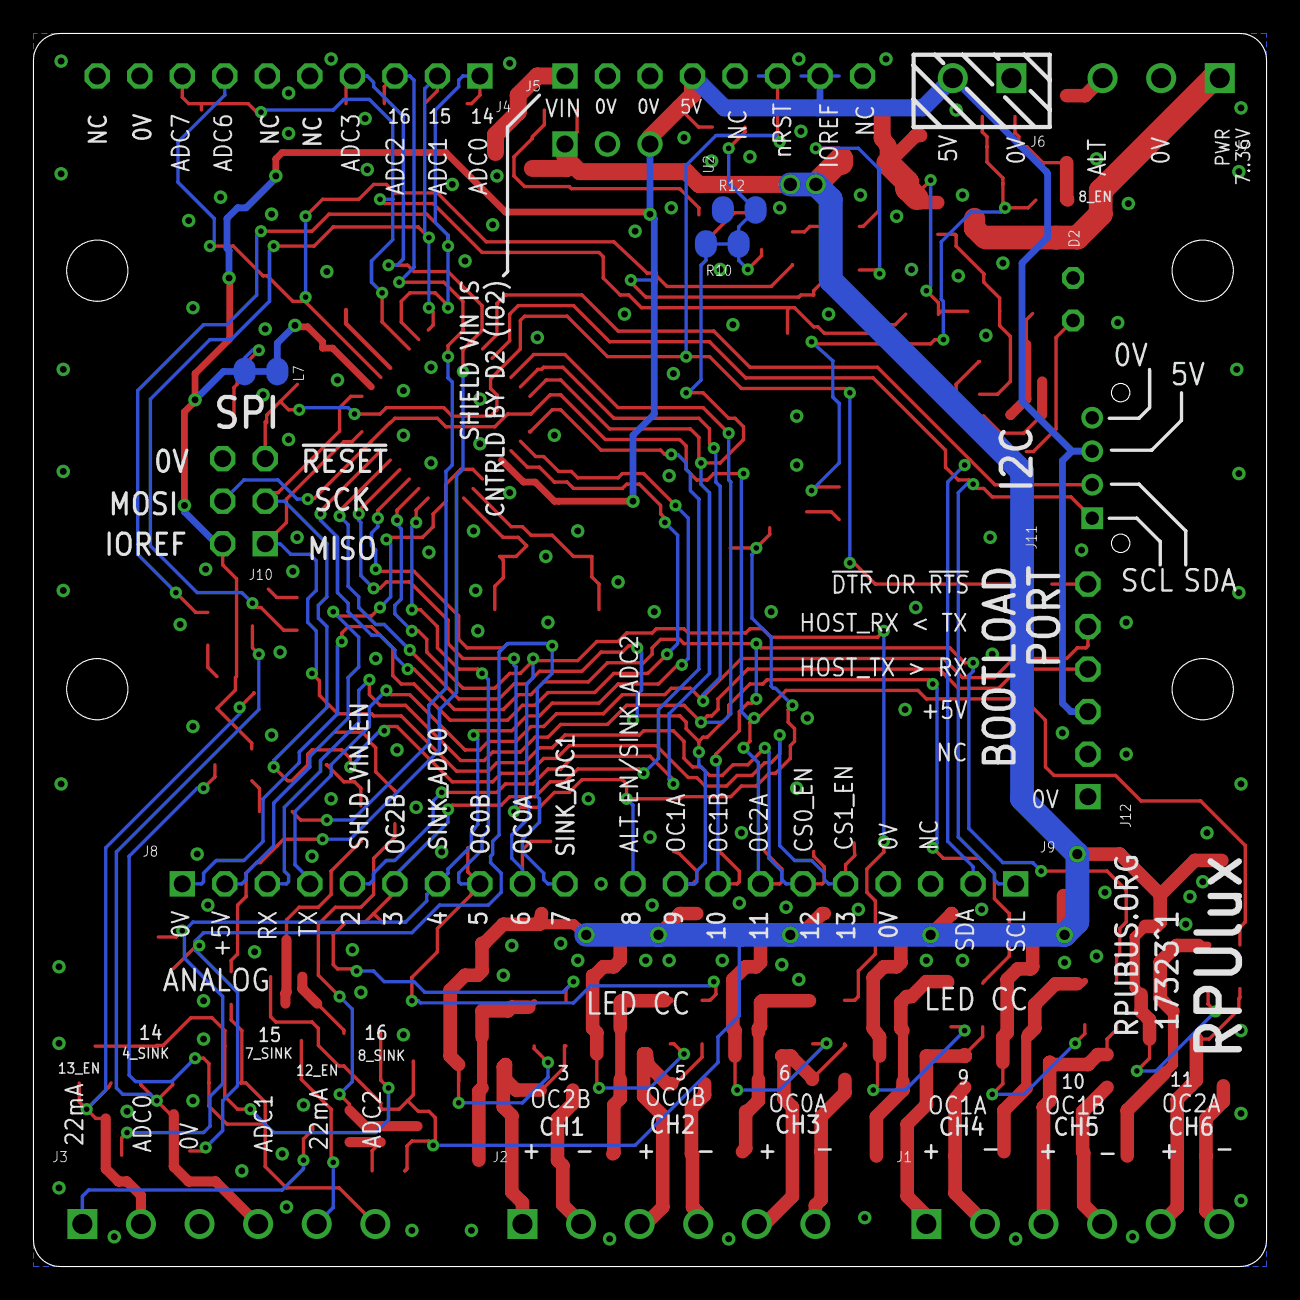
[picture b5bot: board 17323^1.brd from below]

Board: 2 copper layers, 73.7 x 73.7 mm, 137 parts (18 on the bottom side), 79 nets.
